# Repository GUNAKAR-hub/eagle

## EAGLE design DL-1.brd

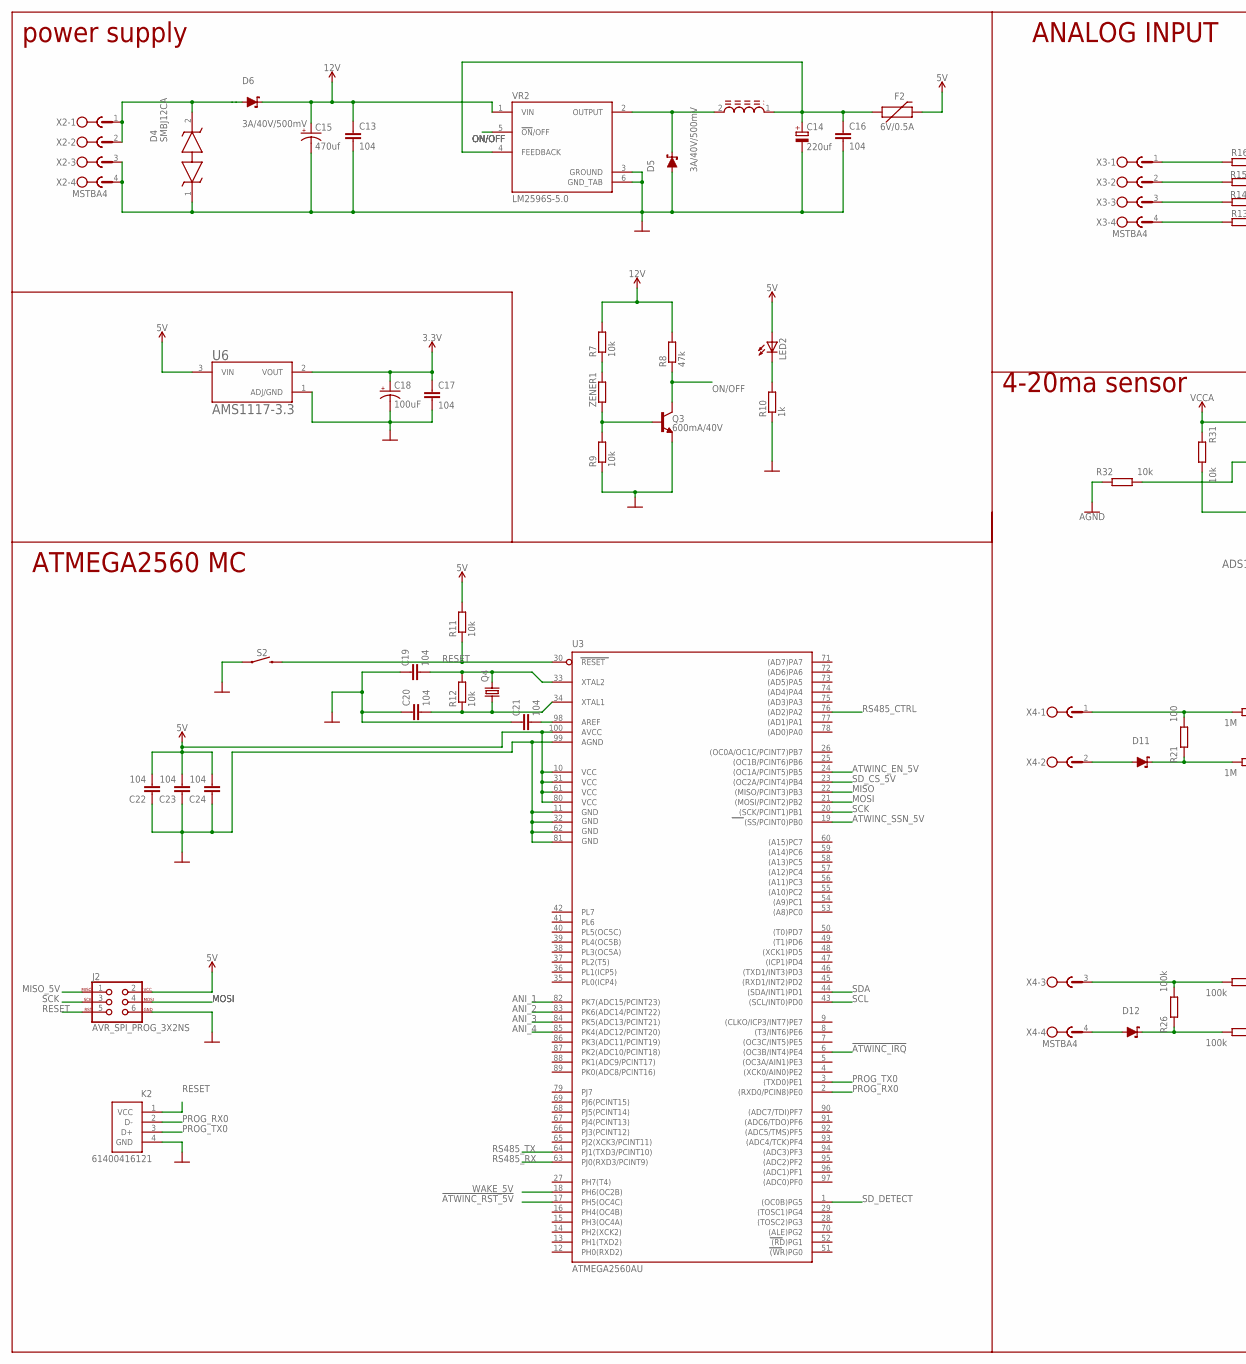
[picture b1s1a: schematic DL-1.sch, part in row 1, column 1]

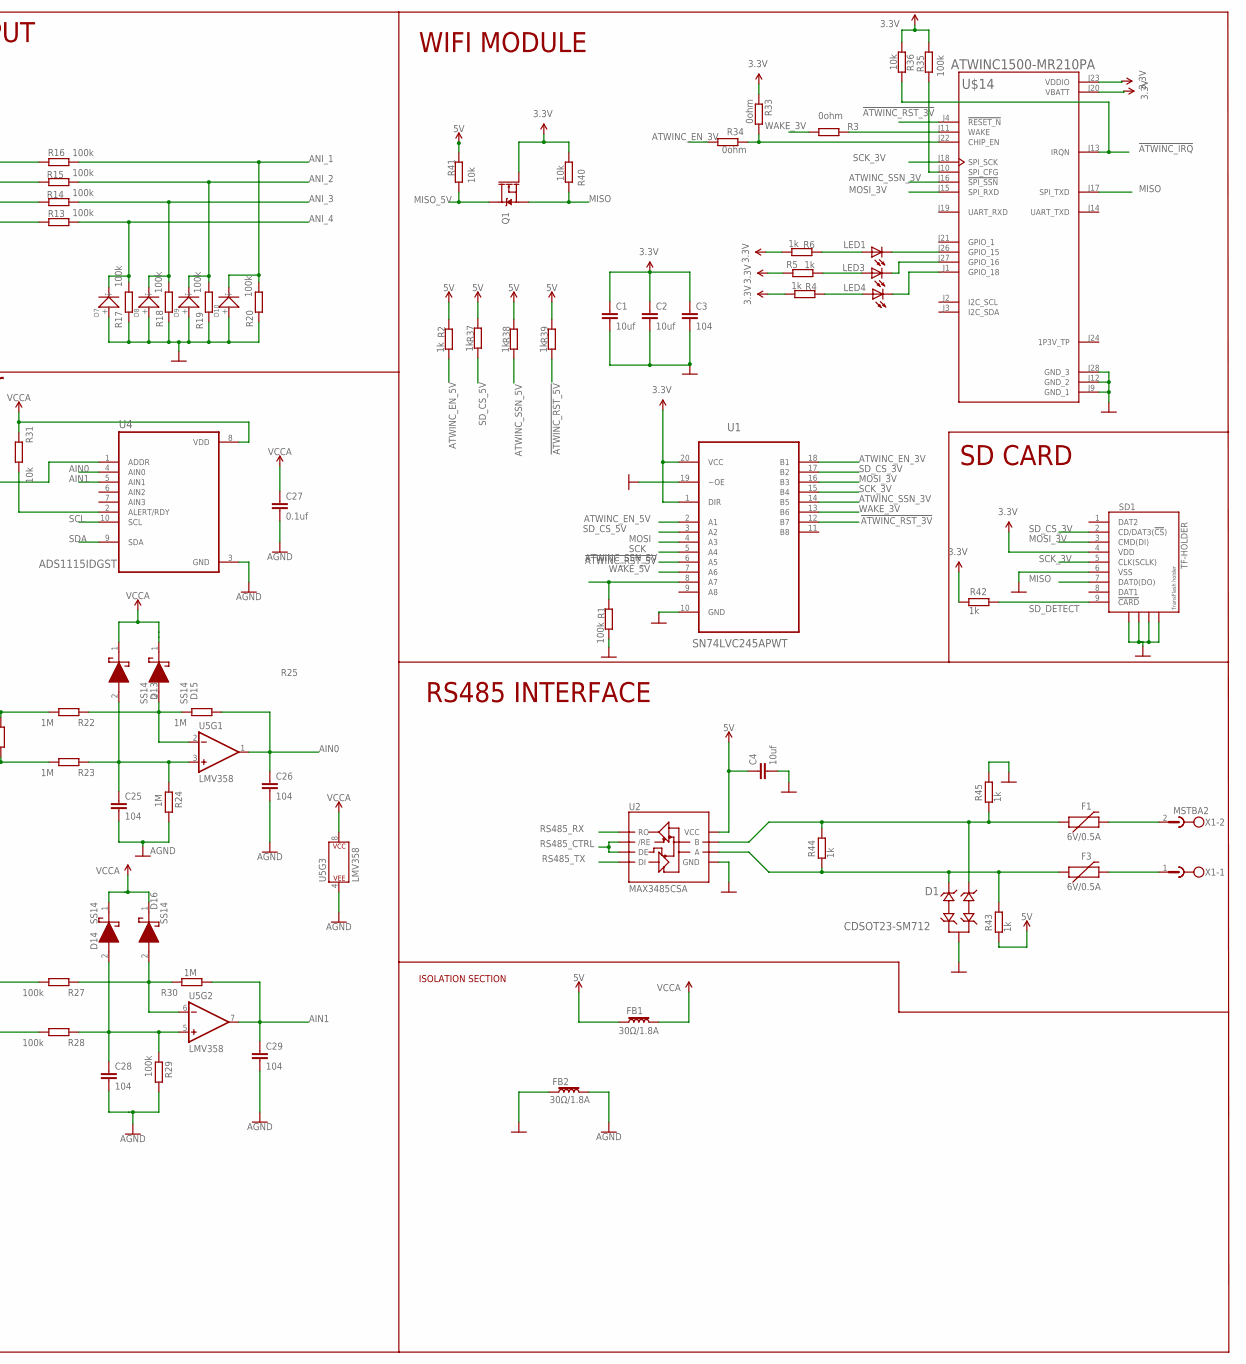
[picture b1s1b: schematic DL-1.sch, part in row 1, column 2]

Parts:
C1, C2, C4: 10uf; C0805
C3, C13, C16, C17, C19, C20, C21, C22, C23, C24, C25, C26, C28, C29: 104; C0805
C14: 220uf; 153CLV-1014
C15: 470uf; E5-8,5
C18: 100uF; NIC_10X10.5_CAP
C27: 0.1uf; C0805
D1: CDSOT23-SM712; SOT-23-3
D4: SMBJ12CA; DIONM5443X244N
D5, D6, D11, D12: 3A/40V/500mV; SMA-DIODE
D7, D8, D9, D10: SMD-DIODE-ZENER-5.1V-500MW(SOD-123); SOD-123
D13, D14, D15, D16: SS14; DIOM5227X270N
F1, F2, F3: 6V/0.5A; 1206
FB1, FB2: 30Ω/1.8A; 0603
J2: AVR_SPI_PROG_3X2NS; 2X3-NS
K2: 61400416121
L2: SRR1260-680M; INDP125125X600N
LED1, LED2, LED3, LED4: LEDCHIP-LED0805; CHIP-LED0805
Q1: 220mA/50V/3.5Ω; SOT23-3
Q3: 600mA/40V; SOT23-3
Q4: CRYSTALHC49S; HC49/S
R1, R13, R14, R15, R16, R17, R18, R19, R20, R26, R27, R28, R29, R35: 100k; M0805
R2, R4, R5, R6, R10, R37, R38, R39, R42, R43, R44, R45: 1k; M0805
R3, R33, R34: 0ohm; M0805
R7, R9, R11, R12, R31, R32, R36, R40, R41: 10k; M0805
R8: 47k; M0805
R21: 100; M0805
R22, R23, R24, R25, R30: 1M; M0805
S2: MOMENTARY-SWITCH-SPST-SMD-6.0X3.5MM; TACTILE_SWITCH_SMD_6.0X3.5MM
SD1: TF-HOLDER; TF-PULL
U1: SN74LVC245APWT; SOP65P640X120-20N
U2: MAX3485CSA; SO08
U3: ATMEGA2560AU; TQFP100
U4: ADS1115IDGST; SOP50P490X110-10N
U5: LMV358; SO08
U6: AMS1117-3.3; SOT229P700X180-4N
U$14: ATWINC1500-MR210PA; ATMEL_ATWINC1500-MR210PA
VR2: LM2596S-5.0; TO170P1524X483-6N
X1: MSTBA2
X2, X3, X4: MSTBA4
ZENER1: R-EU_0204/7; 0204/7

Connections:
3.3V: C1.1, C2.1, C3.1, C17.1, C18.+, Q1.1 (G), R4.2, R5.2, R6.2, R33.1, R35.1, R36.1, R40.1, R42.1, SD1.4 (VDD), U1.1 (DIR), U1.20 (VCC), U6.2 (VOUT), U$14.J20 (VBATT), U$14.J23 (VDDIO)
5V: C4.1, C22.2, C23.2, C24.2, F2.2, FB1.1, J2.2, LED2.A, R2.1, R11.2, R37.1, R38.1, R39.1, R41.1, R43.1, U2.8 (VCC), U3.10 (VCC), U3.31 (VCC1), U3.61 (VCC2), U3.80 (VCC3), U3.100 (AVCC), U6.3 (VIN)
12V: C13.1, C15.+, D6.C, R7.2, R8.2, VR2.1 (VIN)
!ATWINC_IRQ: R36.2, U3.6 ((OC3B/INT4)PE4), U$14.J13 (IRQN)
!ATWINC_RST_3V: U1.12 (B7), U$14.J4 (!RESET_N)
!ATWINC_RST_5V: R1.1, R39.2, U1.8 (A7), U3.17 (PH5(OC4C))
AGND: C25.2, C26.2, C27.2, C28.2, C29.2, FB2.2, R24.1, R29.1, R32.1, U4.3 (GND), U5.4 (P$V-)
AIN0: C26.1, R25.1, U4.4 (AIN0), U5.1 (OUT)
AIN1: C29.1, R30.1, U4.5 (AIN1), U5.7 (OUT)
ANI_1: D10.-, R16.1, R20.2, U3.82 (PK7(ADC15/PCINT23))
ANI_2: D9.-, R15.1, R19.2, U3.83 (PK6(ADC14/PCINT22))
ANI_3: D8.-, R14.1, R18.2, U3.84 (PK5(ADC13/PCINT21))
ANI_4: D7.-, R13.1, R17.2, U3.85 (PK4(ADC12/PCINT20))
ATWINC_EN_3V: R34.1, U1.18 (B1)
ATWINC_EN_5V: R2.2, U1.2 (A1), U3.24 ((OC1A/PCINT5)PB5)
ATWINC_SSN_3V: U1.14 (B5), U$14.J16 (!SPI_SSN)
ATWINC_SSN_5V: R38.2, U1.6 (A5), U3.19 ((SS/PCINT0)PB0)
GND: C1.2, C2.2, C3.2, C4.2, C13.2, C14.-, C15.-, C16.2, C17.2, C18.-, C19.1, C20.1, C21.1, C22.1, C23.1, C24.1, D1.3 (GND), D4.1, D5.A, D7.+, D8.+, D9.+, D10.+, FB2.1, J2.6, K2.4 (GND), Q3.2 (E), R1.2, R9.1, R10.1, R17.1, R18.1, R19.1, R20.1, R45.2, S2.1, SD1.6 (VSS), SD1.S1, SD1.S2, SD1.S3, SD1.S4, U1.10 (GND), U1.19 (~OE), U2.5 (GND), U3.11 (GND), U3.32 (GND1), U3.62 (GND2), U3.81 (GND3), U3.99 (AGND), U6.1 (ADJ/GND), U$14.J9 (GND_1), U$14.J12 (GND_2), U$14.J28 (GND_3), VR2.3 (GROUND), VR2.6 (GND_TAB), X2.3, X2.4
MISO: Q1.2 (S), R40.2, SD1.7 (DAT0(DO)), U3.22 ((MISO/PCINT3)PB3), U$14.J17 (SPI_TXD)
MISO_5V: J2.1, Q1.3 (D), R41.2
MOSI: J2.4, U1.4 (A3), U3.21 ((MOSI/PCINT2)PB2)
MOSI_3V: SD1.3 (CMD(DI)), U1.16 (B3), U$14.J15 (SPI_RXD)
unnamed: LED1.C, U$14.J26 (GPIO_15)
unnamed: LED3.C, U$14.J27 (GPIO_16)
unnamed: D5.C, L2.2, VR2.2 (OUTPUT)
unnamed: LED3.A, R5.1
unnamed: LED1.A, R6.1
unnamed: LED4.C, U$14.J1 (GPIO_18)
unnamed: LED4.A, R4.1
unnamed: D1.2 (IO2), F1.1, R44.2, R45.1, U2.7 (B)
unnamed: R3.1, U$14.J11 (WAKE)
unnamed: R35.2, U$14.J10 (SPI_CFG)
unnamed: C14.+, C16.1, F2.1, L2.1, VR2.4 (FEEDBACK)
unnamed: D4.2, D6.A, X2.1, X2.2
unnamed: LED2.C, R10.2
unnamed: Q3.1 (B), R9.2, ZENER1.1
unnamed: R7.1, ZENER1.2
unnamed: C20.2, Q4.1, R12.1, U3.34 (XTAL1)
unnamed: C19.2, Q4.2, R12.2, U3.33 (XTAL2)
unnamed: C21.2, U3.98 (AREF)
unnamed: R13.2, X3.4
unnamed: R14.2, X3.3
unnamed: R15.2, X3.2
unnamed: R16.2, X3.1
unnamed: R21.2, R22.2, X4.1
unnamed: D11.C, R21.1, R23.2
unnamed: C25.1, D13.2 (A), R23.1, R24.2, U5.3 (+IN)
unnamed: D15.2 (A), R22.1, R25.2, U5.2 (-IN)
unnamed: D11.A, X4.2
unnamed: R26.2, R27.2, X4.3
unnamed: D12.C, R26.1, R28.2
unnamed: C28.1, D14.2 (A), R28.1, R29.2, U5.5 (+IN)
unnamed: D16.2 (A), R27.1, R30.2, U5.6 (-IN)
unnamed: D12.A, X4.4
unnamed: R31.2, U4.2 (ALERT/RDY)
unnamed: R32.2, U4.1 (ADDR)
unnamed: D1.1 (IO1), F3.1, R43.2, R44.1, U2.6 (A)
unnamed: R33.2, R34.2, U$14.J22 (CHIP_EN)
unnamed: F1.2, X1.2
unnamed: F3.2, X1.1
ON/OFF: Q3.3 (C), R8.1, VR2.5 (!ON!/OFF)
PROG_RX0: K2.2 (D-), U3.2 ((RXD0/PCIN8)PE0)
PROG_TX0: K2.3 (D+), U3.3 ((TXD0)PE1)
RESET: J2.5, K2.1 (VCC), R11.1, S2.2, U3.30 (RESET)
RS485_CTRL: U2.2 (/RE), U2.3 (DE), U3.76 ((AD2)PA2)
RS485_RX: U2.1 (RO), U3.63 (PJ0(RXD3/PCINT9))
RS485_TX: U2.4 (DI), U3.64 (PJ1(TXD3/PCINT10))
SCK: J2.3, U1.5 (A4), U3.20 ((SCK/PCINT1)PB1)
SCK_3V: SD1.5 (CLK(SCLK)), U1.15 (B4), U$14.J18 (SPI_SCK)
SCL: U3.43 ((SCL/INT0)PD0), U4.10 (SCL)
SDA: U3.44 ((SDA/INT1)PD1), U4.9 (SDA)
SD_CS_3V: SD1.2 (CD/DAT3(!CS!)), U1.17 (B2)
SD_CS_5V: R37.2, U1.3 (A2), U3.23 ((OC2A/PCINT4)PB4)
SD_DETECT: R42.2, SD1.9 (!CARD), U3.1 ((OC0B)PG5)
VCCA: C27.1, D13.1 (K), D14.1 (K), D15.1 (K), D16.1 (K), FB1.2, R31.1, U4.8 (VDD), U5.8 (P$V+)
WAKE_3V: R3.2, U1.13 (B6)
WAKE_5V: U1.7 (A6), U3.18 (PH6(OC2B))

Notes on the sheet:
power supply
ATMEGA2560 MC
ANALOG INPUT
4-20ma sensor
WIFI MODULE
SD CARD
RS485 INTERFACE
ISOLATION SECTION

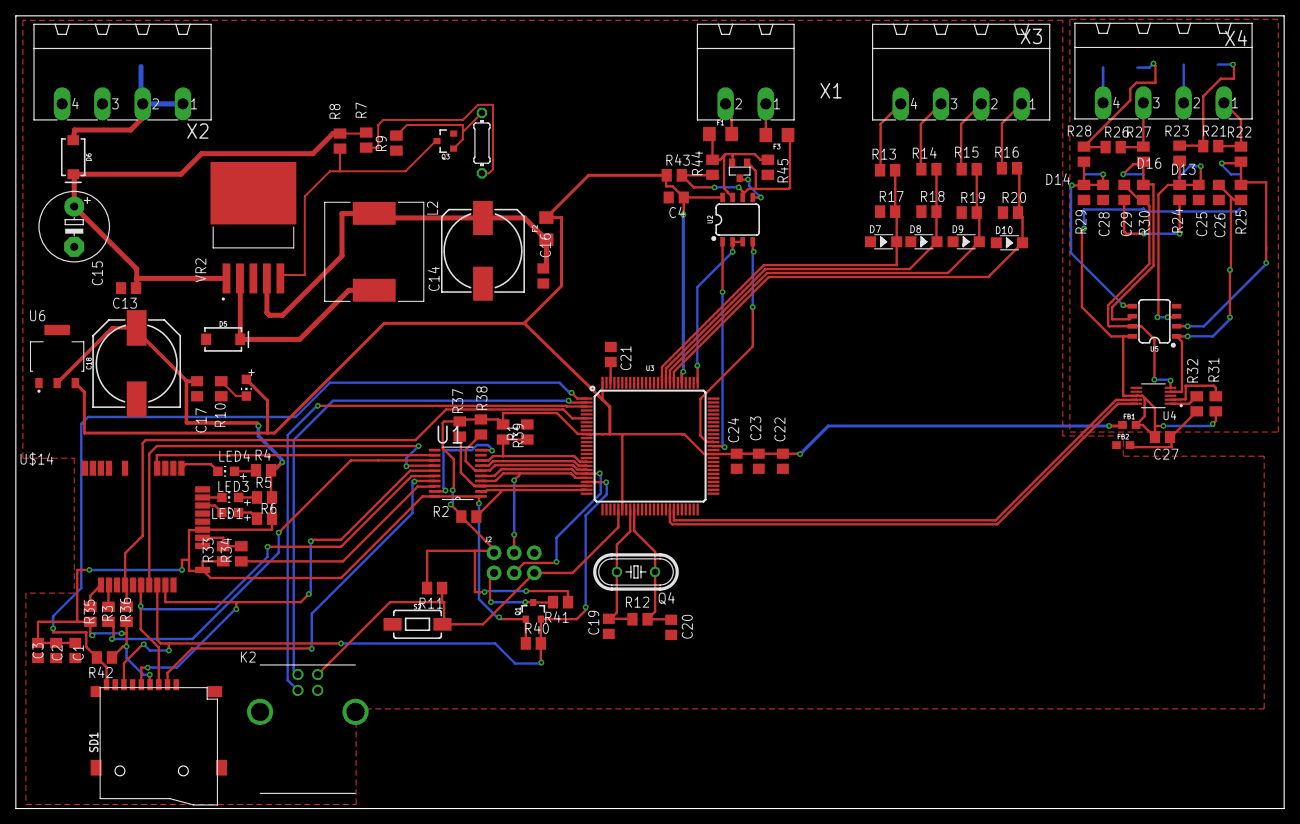
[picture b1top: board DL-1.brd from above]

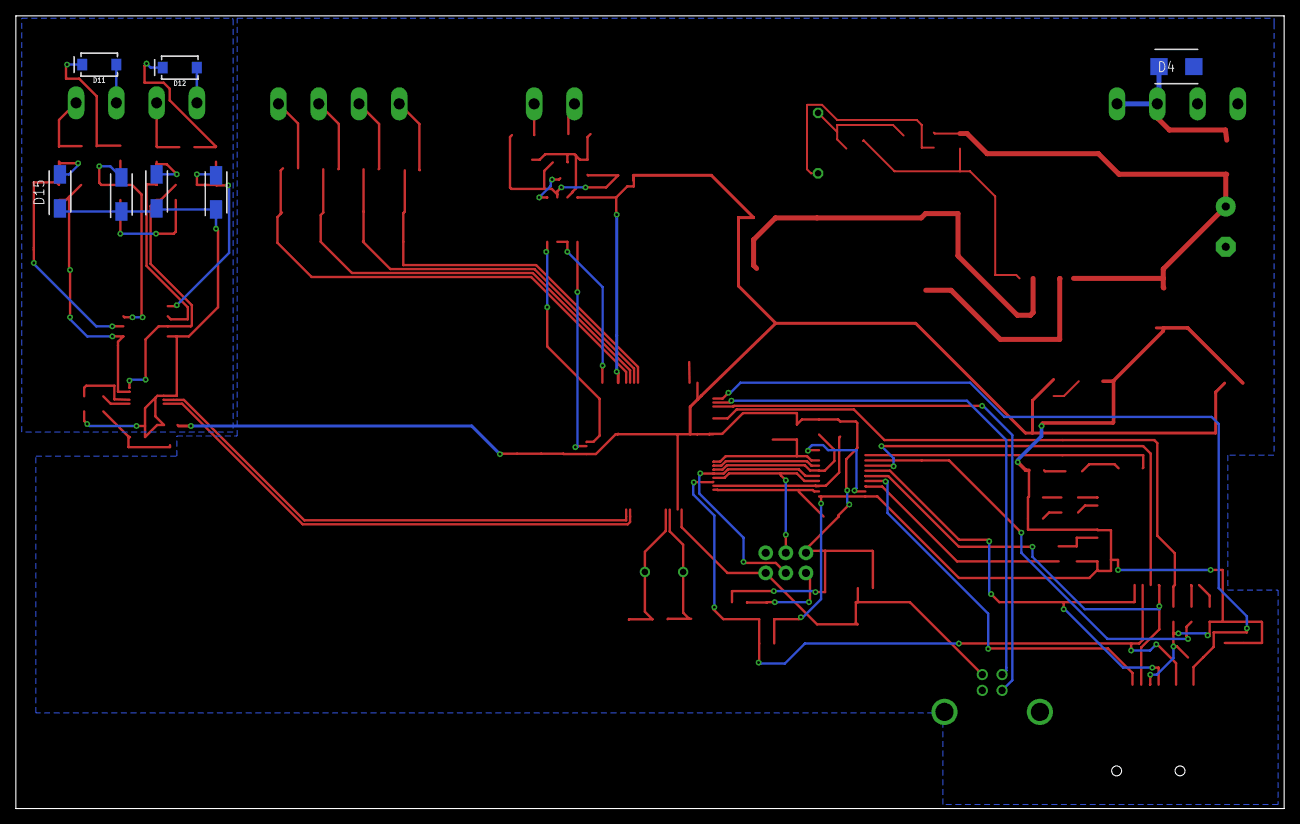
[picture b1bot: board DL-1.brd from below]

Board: 2 copper layers, 160.0 x 100.0 mm, 110 parts (7 on the bottom side), 77 nets.

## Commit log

2021-05-22 Create arduino code

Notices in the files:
parts and their libraries:
SparkFun-Capacitors: Licensing: Creative Commons ShareAlike 4.0 International - https://creativecommons.org/licenses/by-sa/4.0
Wuerth_Elektronik_eiCan_Communication_Co: Copyright: Würth Elektronik
